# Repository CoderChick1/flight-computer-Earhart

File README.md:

# flight-computer-Earhart
Flight computer capable of dual deploy of pyrotechnics, gps tracking, and data-logging. Live telemetry can be implemented with an external board, meant for use with an Adafruit LoRa 433MHz module.

This is my first ever attempt at a pcb- had a lot of problems

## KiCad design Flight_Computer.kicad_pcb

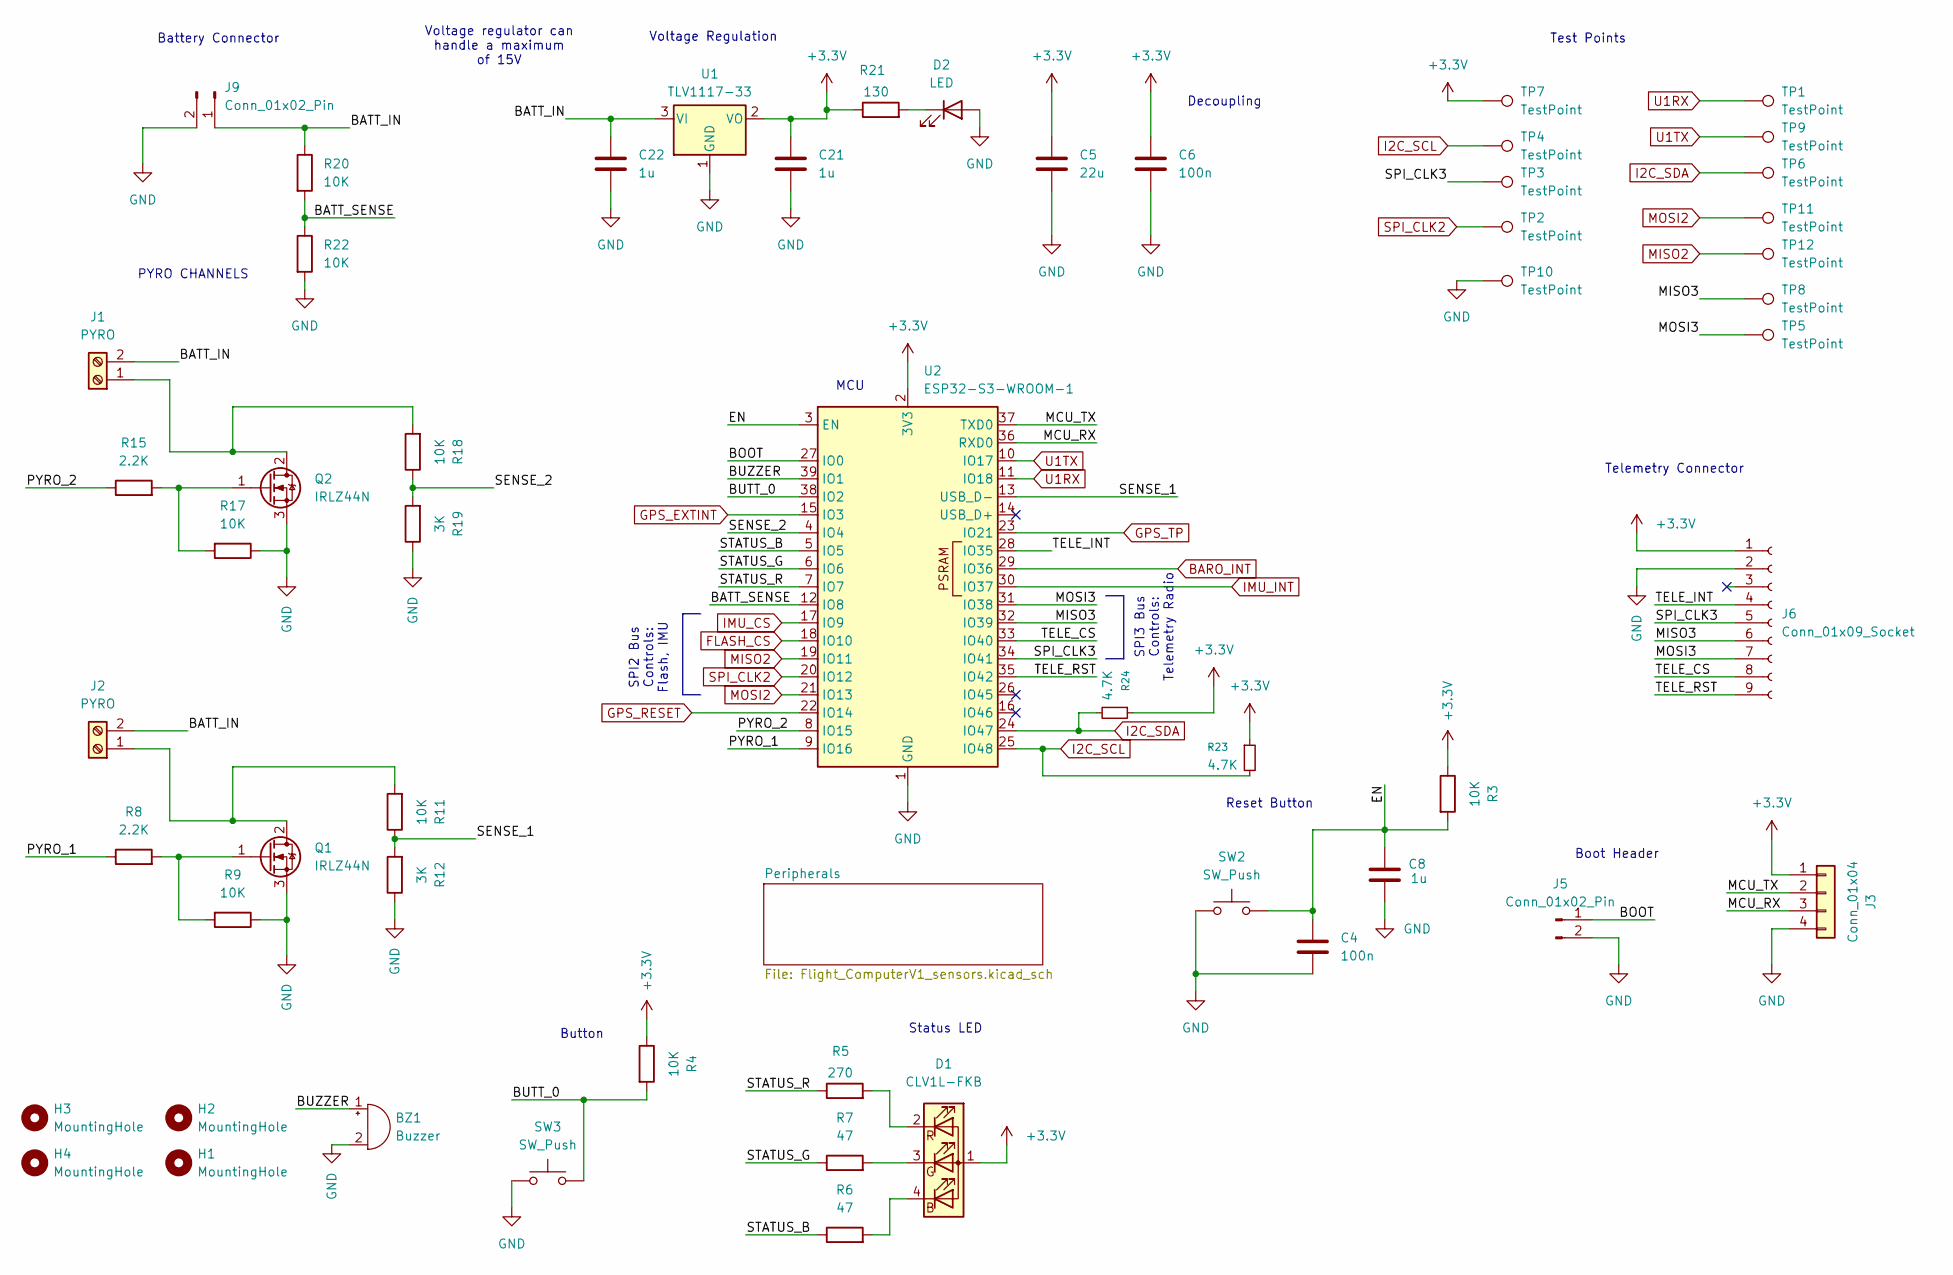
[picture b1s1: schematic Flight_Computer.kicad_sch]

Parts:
BZ1: Buzzer; Buzzer_12x9.5RM7.6
C4, C6: 100n; C_0805_2012Metric
C5: 22u; C_0805_2012Metric
C8, C21, C22: 1u; C_0805_2012Metric
D1: CLV1L-FKB; LED_Cree-PLCC4_3.2x2.8mm_CCW
D2: LED; LED_0603_1608Metric
H1, H2, H3, H4: MountingHole; MountingHole_3mm
J1, J2: PYRO; 282837-2_TYC
J3: Conn_01x04; PinHeader_1x04_P2.54mm_Vertical
J5: Conn_01x02_Pin; PinHeader_1x02_P2.54mm_Vertical
J6: Conn_01x09_Socket; PinSocket_1x09_P2.54mm_Vertical
J9: Conn_01x02_Pin; JST_PH_B2B-PH-K_1x02_P2.00mm_Vertical
Q1, Q2: IRLZ44N; TO-220-3_Vertical
R3, R4, R9, R11, R17, R18, R20, R22: 10K; R_0805_2012Metric
R5: 270; R_0805_2012Metric
R6, R7: 47; R_0805_2012Metric
R8, R15: 2.2K; R_0805_2012Metric
R12, R19: 3K; R_0805_2012Metric
R21: 130; R_0805_2012Metric
R23, R24: 4.7K; R_0805_2012Metric
SW2, SW3: SW_Push; SW_SPST_PTS810
TP1, TP2, TP3, TP4, TP5, TP6, TP7, TP8, TP9, TP10, TP11, TP12: TestPoint; TestPoint_Pad_D2.0mm
U1: TLV1117-33; SOT-223-3_TabPin2
U2: ESP32-S3-WROOM-1

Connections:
+3.3V: C5.1, C6.1, C21.1, D1.1 (A), J3.1, J6.1, R3.1, R4.1, R21.1, R23.1, R24.1, TP7.1, U1.2 (VO), U2.2 (3V3); also elsewhere on the board
/BATT_IN: C22.1, J1.2, J2.2, J9.1, R20.1, U1.3 (VI)
/BATT_SENSE: R20.2, R22.1, U2.12 (IO8)
/BOOT: J5.1, U2.27 (IO0)
/BUTT_0: R4.2, SW3.2, U2.38 (IO2)
/BUZZER: BZ1.1 (+), U2.39 (IO1)
/EN: C4.1, C8.2, R3.2, SW2.2, U2.3 (EN)
/MCU_RX: J3.3, U2.36 (RXD0)
/MCU_TX: J3.2, U2.37 (TXD0)
/MISO3: J6.6, TP8.1, U2.32 (IO39)
/MOSI3: J6.7, TP5.1, U2.31 (IO38)
/PYRO_1: R8.1, U2.9 (IO16)
/PYRO_2: R15.1, U2.8 (IO15)
/SENSE_1: R11.1, R12.2, U2.13 (USB_D-)
/SENSE_2: R18.1, R19.2, U2.4 (IO4)
/SPI_CLK3: J6.5, TP3.1, U2.34 (IO41)
/STATUS_B: R6.1, U2.5 (IO5)
/STATUS_G: R7.1, U2.6 (IO6)
/STATUS_R: R5.1, U2.7 (IO7)
/TELE_CS: J6.8, U2.33 (IO40)
/TELE_INT: J6.4, U2.28 (IO35)
/TELE_RST: J6.9, U2.35 (IO42)
BARO_INT: U2.29 (IO36); also elsewhere on the board
FLASH_CS: U2.18 (IO10); also elsewhere on the board
GND: BZ1.2 (-), C4.2, C5.2, C6.2, C8.1, C21.2, C22.2, D2.2 (A), J3.4, J5.2, J6.2, J9.2, Q1.3 (S), Q2.3 (S), R9.1, R12.1, R17.1, R19.1, R22.2, SW2.1, SW3.1, TP10.1, U1.1 (GND), U2.1 (GND), U2.40 (GND), U2.41 (GND); also elsewhere on the board
GPS_EXTINT: U2.15 (IO3); also elsewhere on the board
GPS_RESET: U2.22 (IO14); also elsewhere on the board
GPS_TP: U2.23 (IO21); also elsewhere on the board
I2C_SCL: R23.2, TP4.1, U2.25 (IO48); also elsewhere on the board
I2C_SDA: R24.2, TP6.1, U2.24 (IO47); also elsewhere on the board
IMU_CS: U2.17 (IO9); also elsewhere on the board
IMU_INT: U2.30 (IO37); also elsewhere on the board
MISO2: TP12.1, U2.19 (IO11); also elsewhere on the board
MOSI2: TP11.1, U2.21 (IO13); also elsewhere on the board
unnamed: D1.4 (BK), R6.2
unnamed: D1.3 (GK), R7.2
unnamed: D1.2 (RK), R5.2
unnamed: D2.1 (K), R21.2
unnamed: J1.1, Q2.2 (D), R18.2
unnamed: J2.1, Q1.2 (D), R11.2
unnamed: Q1.1 (G), R8.2, R9.2
unnamed: Q2.1 (G), R15.2, R17.2
SPI_CLK2: TP2.1, U2.20 (IO12); also elsewhere on the board
U1RX: TP1.1, U2.11 (IO18); also elsewhere on the board
U1TX: TP9.1, U2.10 (IO17); also elsewhere on the board

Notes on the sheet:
Status LED
Reset Button
Boot Header
Voltage regulator can handle a maximum of 15V
Battery Connector
Button
PYRO CHANNELS
Decoupling
SPI2 Bus Controls: Flash, IMU
Telemetry Connector
Test Points
Voltage Regulation
MCU
SPI3 Bus Controls: Telemetry Radio

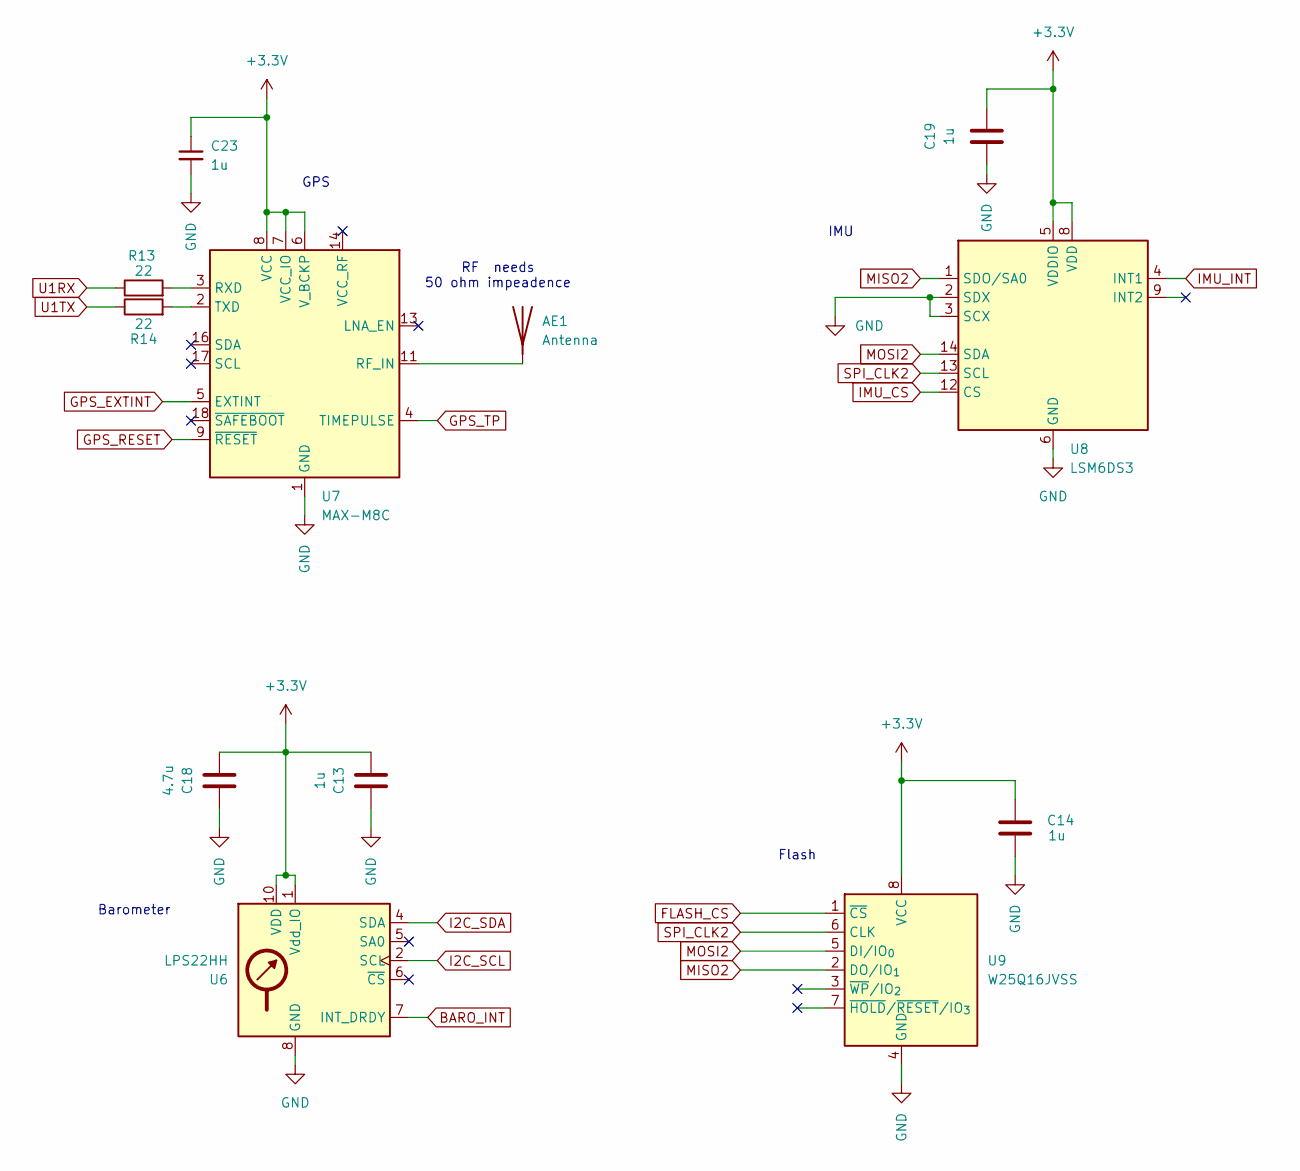
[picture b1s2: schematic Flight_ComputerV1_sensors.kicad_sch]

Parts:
AE1: Antenna; Untitled
C13, C14, C19, C23: 1u; C_0805_2012Metric
C18: 4.7u; C_0805_2012Metric
R13, R14: 22; R_0805_2012Metric
U6: LPS22HH; ST_HLGA-10_2x2mm_P0.5mm_LayoutBorder3x2y
U7: MAX-M8C; ublox_MAX
U8: LSM6DS3; LGA-14_3x2.5mm_P0.5mm_LayoutBorder3x4y
U9: W25Q16JVSS; SOIC-8_5.3x5.3mm_P1.27mm

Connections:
+3.3V: C13.1, C14.2, C18.1, C19.2, C23.1, U6.1 (Vdd_IO), U6.10 (VDD), U7.6 (V_BCKP), U7.7 (VCC_IO), U7.8 (VCC), U8.5 (VDDIO), U8.8 (VDD), U9.8 (VCC); also elsewhere on the board
BARO_INT: U6.7 (INT_DRDY); also elsewhere on the board
FLASH_CS: U9.1 (~CS); also elsewhere on the board
GND: C13.2, C14.1, C18.2, C19.1, C23.2, U6.3 (GND), U6.8 (GND), U6.9 (GND), U7.1 (GND), U7.10 (GND), U7.12 (GND), U8.2 (SDX), U8.3 (SCX), U8.6 (GND), U8.7 (GND), U9.4 (GND); also elsewhere on the board
GPS_EXTINT: U7.5 (EXTINT); also elsewhere on the board
GPS_RESET: U7.9 (~RESET); also elsewhere on the board
GPS_TP: U7.4 (TIMEPULSE); also elsewhere on the board
I2C_SCL: U6.2 (SCL); also elsewhere on the board
I2C_SDA: U6.4 (SDA); also elsewhere on the board
IMU_CS: U8.12 (CS); also elsewhere on the board
IMU_INT: U8.4 (INT1); also elsewhere on the board
MISO2: U8.1 (SDO/SA0), U9.2 (DO/IO_{1}); also elsewhere on the board
MOSI2: U8.14 (SDA), U9.5 (DI/IO_{0}); also elsewhere on the board
unnamed: AE1.1 (A), U7.11 (RF_IN)
unnamed: R13.2, U7.3 (RXD)
unnamed: R14.2, U7.2 (TXD)
SPI_CLK2: U8.13 (SCL), U9.6 (CLK); also elsewhere on the board
U1RX: R13.1; also elsewhere on the board
U1TX: R14.1; also elsewhere on the board

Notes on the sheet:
GPS
IMU
RF needs 50 ohm impeadence
Flash
Barometer

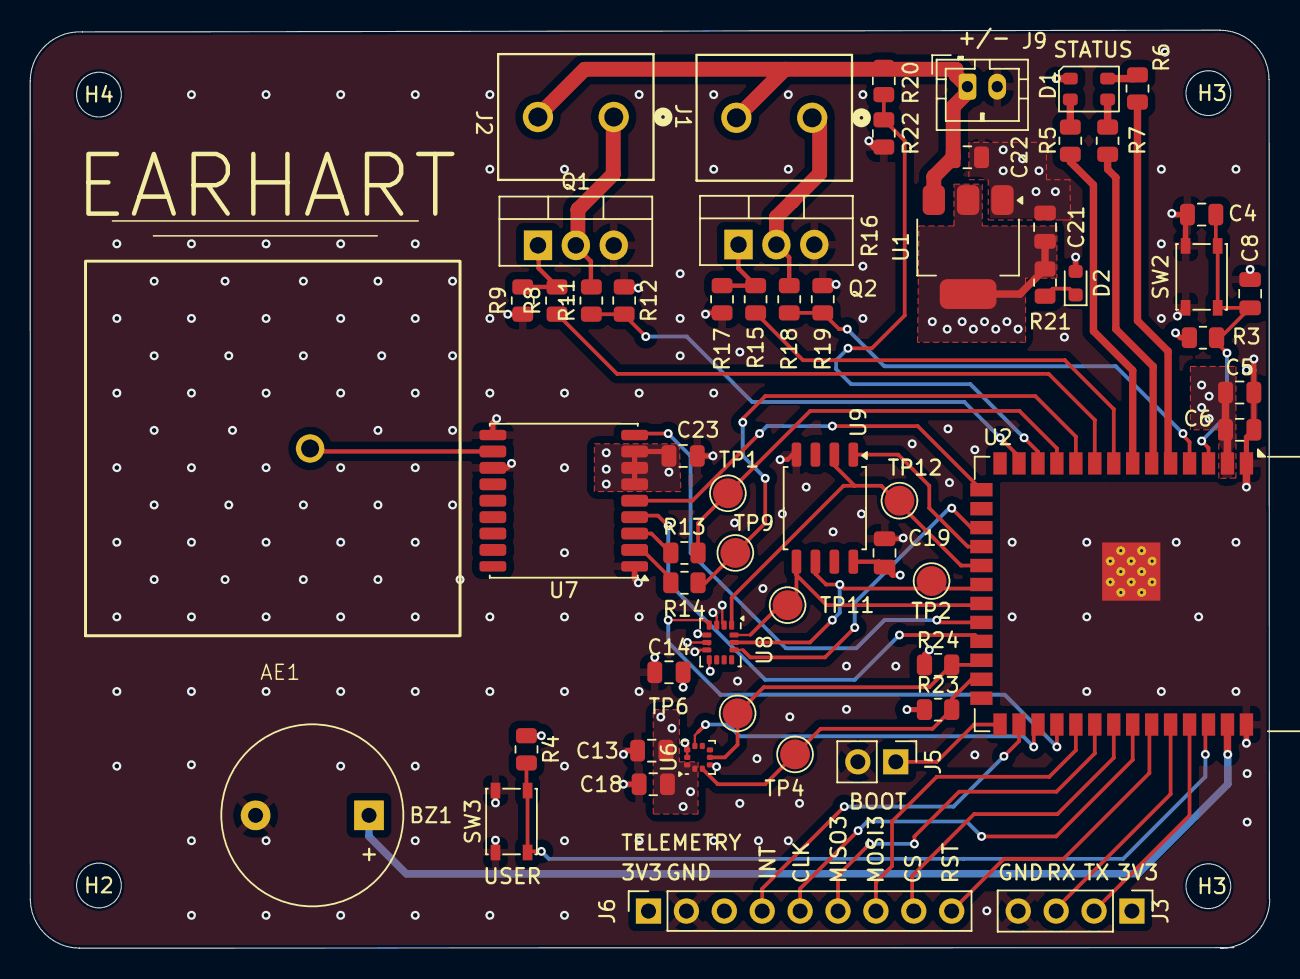
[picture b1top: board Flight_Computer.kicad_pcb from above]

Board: 4 copper layers, 83.1 x 61.5 mm, 62 parts (0 on the bottom side), 48 nets.

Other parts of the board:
H3#2: MountingHole; MountingHole_3mm

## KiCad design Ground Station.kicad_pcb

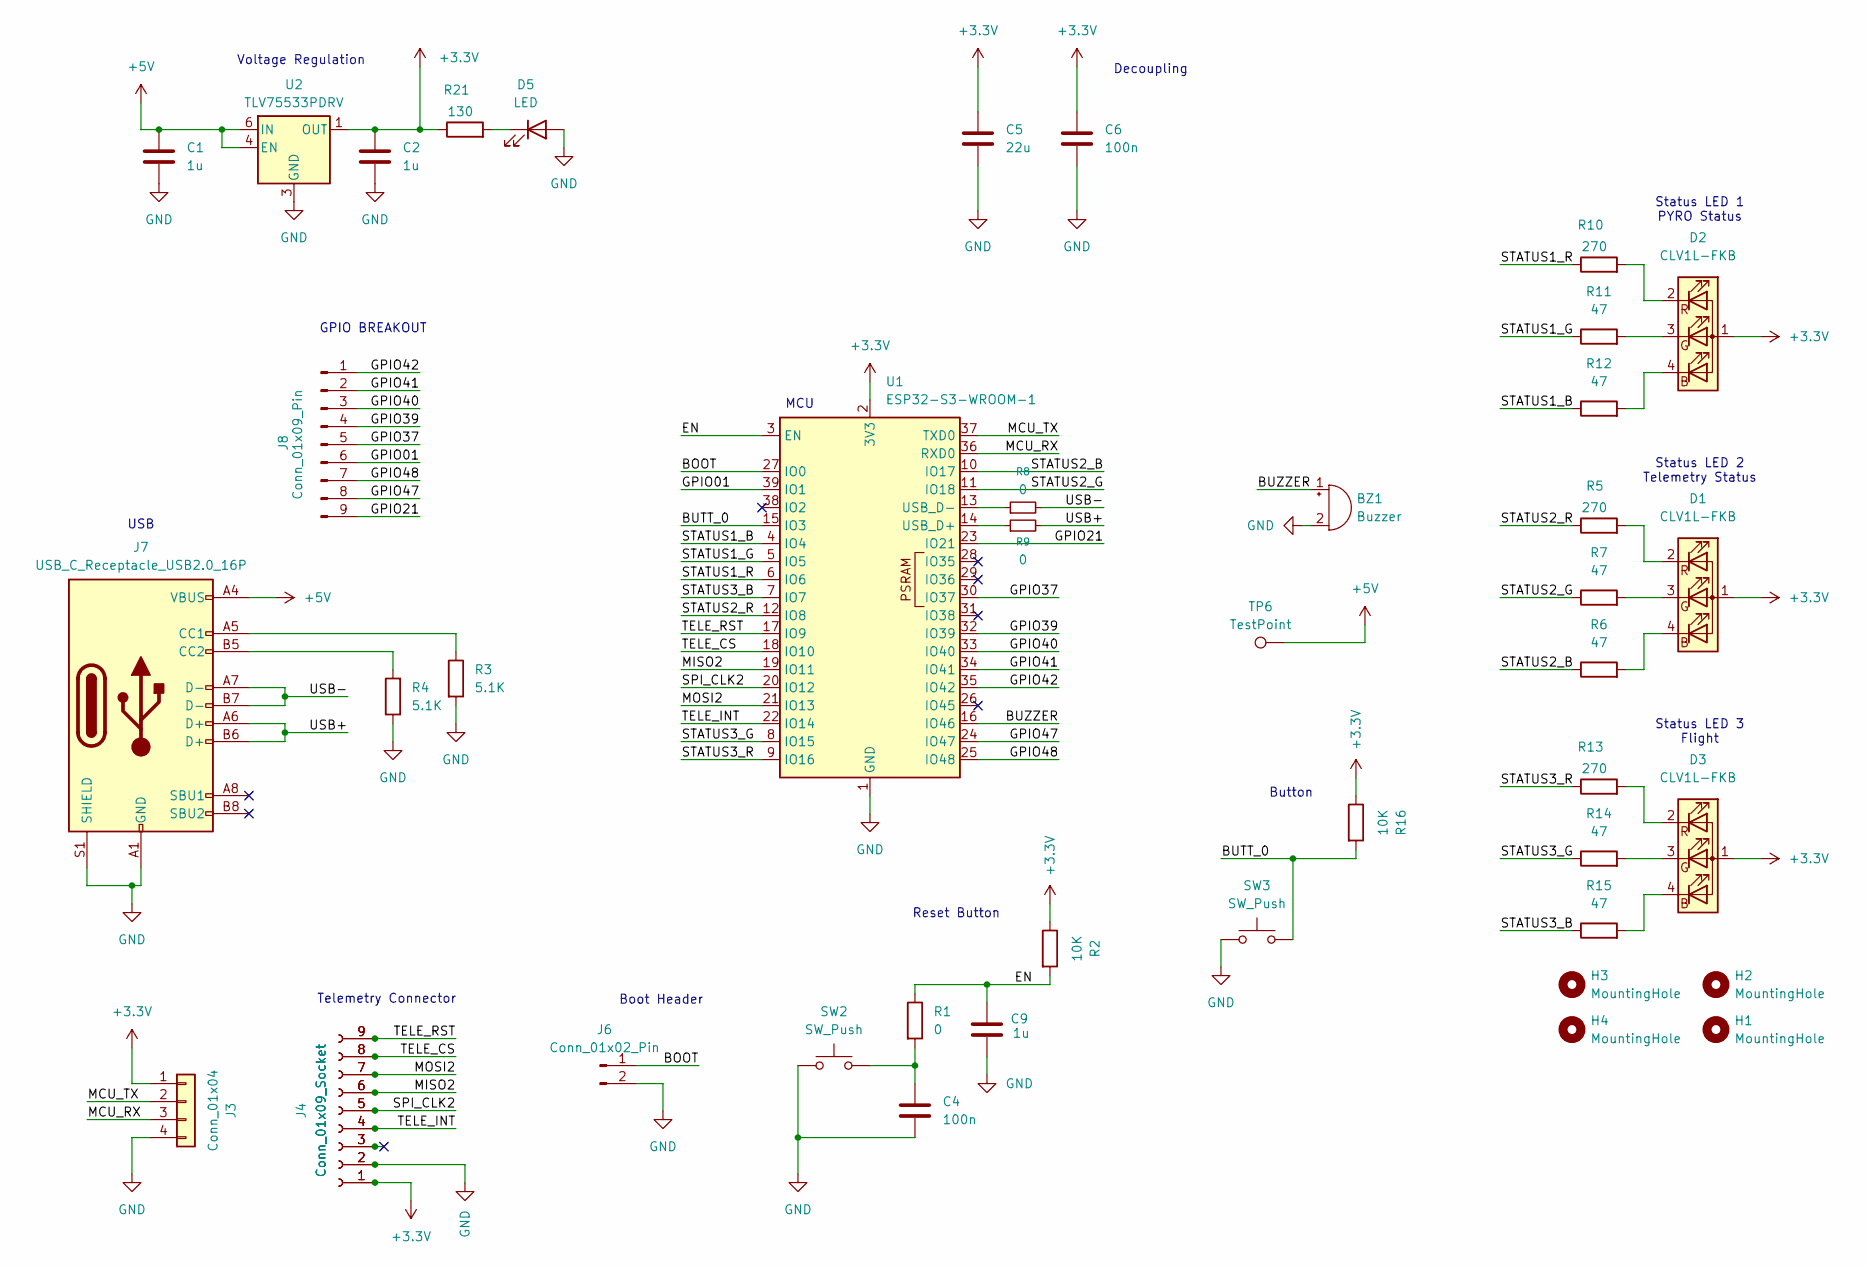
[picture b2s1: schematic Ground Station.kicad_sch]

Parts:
BZ1: Buzzer; Buzzer_12x9.5RM7.6
C1, C2, C9: 1u; C_0805_2012Metric
C4, C6: 100n; C_0805_2012Metric
C5: 22u; C_0805_2012Metric
D1, D2, D3: CLV1L-FKB; LED_Cree-PLCC4_3.2x2.8mm_CCW
D5: LED; LED_0603_1608Metric
H1, H2, H3, H4: MountingHole; MountingHole_3mm
J3: Conn_01x04; PinHeader_1x04_P2.54mm_Vertical
J4, J5: Conn_01x09_Socket; PinSocket_1x09_P2.54mm_Vertical
J6: Conn_01x02_Pin; PinHeader_1x02_P2.54mm_Vertical
J7: USB_C_Receptacle_USB2.0_16P; USB_C_Receptacle_GCT_USB4105-xx-A_16P_TopMnt_Horizontal
J8: Conn_01x09_Pin; PinHeader_1x09_P2.54mm_Vertical
R1, R8, R9: 0; R_0805_2012Metric
R2, R16: 10K; R_0805_2012Metric
R3, R4: 5.1K; R_0805_2012Metric
R5, R10, R13: 270; R_0805_2012Metric
R6, R7, R11, R12, R14, R15: 47; R_0805_2012Metric
R21: 130; R_0805_2012Metric
SW2, SW3: SW_Push; SW_SPST_PTS810
TP6: TestPoint; TestPoint_Pad_D2.0mm
U1: ESP32-S3-WROOM-1
U2: TLV75533PDRV; SOT-223

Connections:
+3.3V: C2.1, C5.1, C6.1, D1.1 (A), D2.1 (A), D3.1 (A), J3.1, J4.1, J5.1, R2.1, R16.1, R21.1, U1.2 (3V3), U2.1 (OUT)
+5V: C1.1, J7.A4 (VBUS), J7.A9 (VBUS), J7.B4 (VBUS), J7.B9 (VBUS), TP6.1, U2.4 (EN), U2.6 (IN)
/BOOT: J6.1, U1.27 (IO0)
/BUTT_0: R16.2, SW3.2, U1.15 (IO3)
/BUZZER: BZ1.1 (+), U1.16 (IO46)
/EN: C9.2, R1.1, R2.2, U1.3 (EN)
/GPIO01: J8.6, U1.39 (IO1)
/GPIO21: J8.9, U1.23 (IO21)
/GPIO37: J8.5, U1.30 (IO37)
/GPIO39: J8.4, U1.32 (IO39)
/GPIO40: J8.3, U1.33 (IO40)
/GPIO41: J8.2, U1.34 (IO41)
/GPIO42: J8.1, U1.35 (IO42)
/GPIO47: J8.8, U1.24 (IO47)
/GPIO48: J8.7, U1.25 (IO48)
/MCU_RX: J3.3, U1.36 (RXD0)
/MCU_TX: J3.2, U1.37 (TXD0)
/MISO2: J4.6, J5.6, U1.19 (IO11)
/MOSI2: J4.7, J5.7, U1.21 (IO13)
/SPI_CLK2: J4.5, J5.5, U1.20 (IO12)
/STATUS1_B: R12.1, U1.4 (IO4)
/STATUS1_G: R11.1, U1.5 (IO5)
/STATUS1_R: R10.1, U1.6 (IO6)
/STATUS2_B: R6.1, U1.10 (IO17)
/STATUS2_G: R7.1, U1.11 (IO18)
/STATUS2_R: R5.1, U1.12 (IO8)
/STATUS3_B: R15.1, U1.7 (IO7)
/STATUS3_G: R14.1, U1.8 (IO15)
/STATUS3_R: R13.1, U1.9 (IO16)
/TELE_CS: J4.8, J5.8, U1.18 (IO10)
/TELE_INT: J4.4, J5.4, U1.22 (IO14)
/TELE_RST: J4.9, J5.9, U1.17 (IO9)
/USB+: J7.A6 (D+), J7.B6 (D+), R9.2
/USB-: J7.A7 (D-), J7.B7 (D-), R8.2
GND: BZ1.2 (-), C1.2, C2.2, C4.2, C5.2, C6.2, C9.1, D5.2 (A), J3.4, J4.2, J5.2, J6.2, J7.A1 (GND), J7.A12 (GND), J7.B1 (GND), J7.B12 (GND), J7.S1 (SHIELD), R3.2, R4.1, SW2.1, SW3.1, U1.1 (GND), U1.40 (GND), U1.41 (GND), U2.3 (GND), U2.7 (GND)
unnamed: C4.1, R1.2, SW2.2
unnamed: D1.4 (BK), R6.2
unnamed: D1.3 (GK), R7.2
unnamed: D1.2 (RK), R5.2
unnamed: D2.4 (BK), R12.2
unnamed: D2.3 (GK), R11.2
unnamed: D2.2 (RK), R10.2
unnamed: D3.4 (BK), R15.2
unnamed: D3.3 (GK), R14.2
unnamed: D3.2 (RK), R13.2
unnamed: D5.1 (K), R21.2
unnamed: J4.3, J5.3
unnamed: J7.A5 (CC1), R3.1
unnamed: J7.B5 (CC2), R4.2
unnamed: R9.1, U1.14 (USB_D+)
unnamed: R8.1, U1.13 (USB_D-)

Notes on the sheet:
Status LED 3 Flight
Telemetry Connector
Voltage Regulation
Status LED 2 Telemetry Status
Boot Header
Status LED 1 PYRO Status
MCU
Decoupling
USB
Reset Button
GPIO BREAKOUT
Button

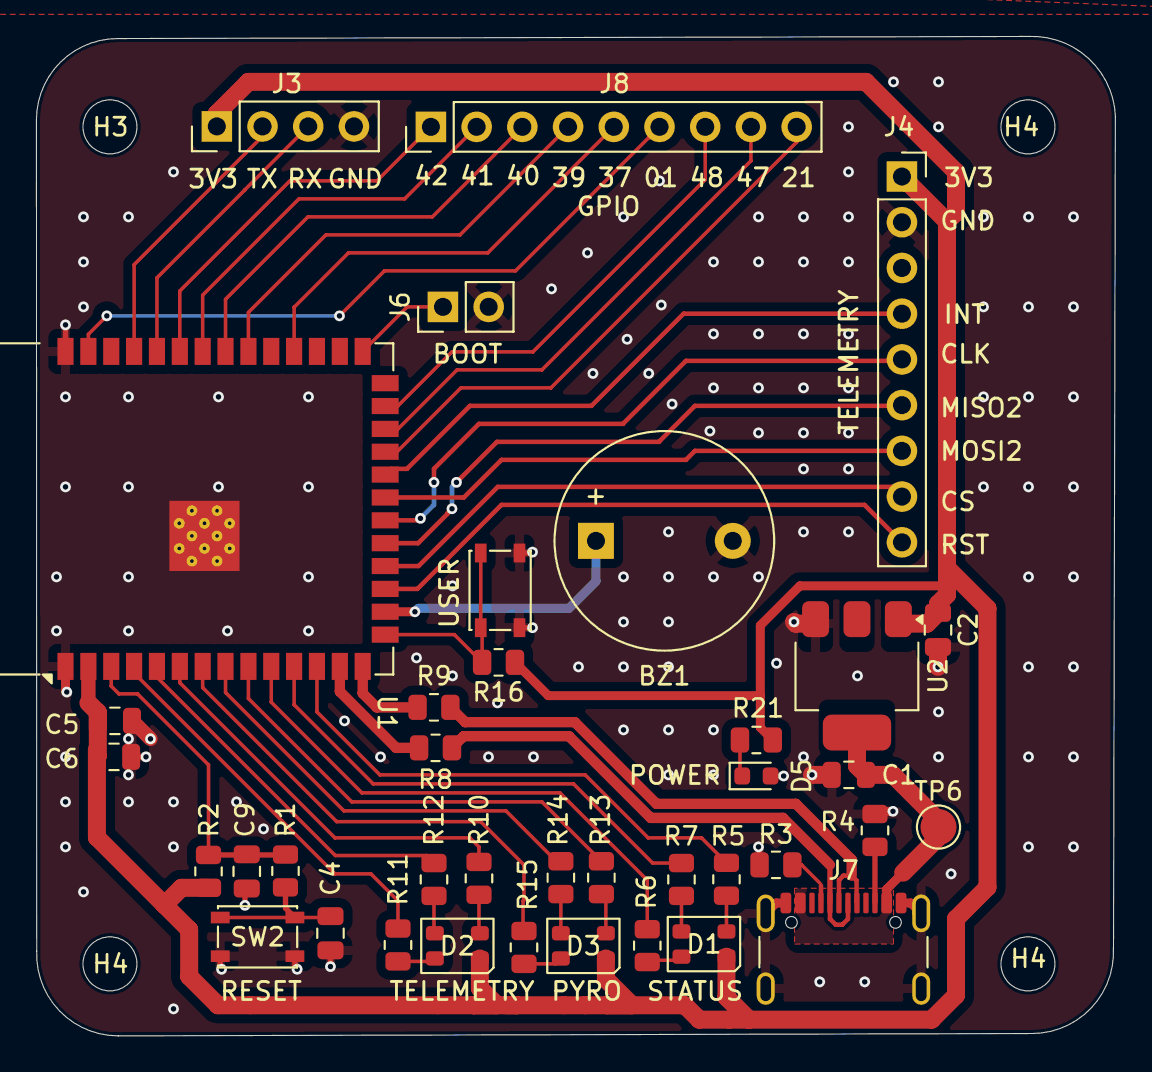
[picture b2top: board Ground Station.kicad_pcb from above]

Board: 2 copper layers, 59.9 x 55.5 mm, 42 parts (0 on the bottom side), 50 nets.

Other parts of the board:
H4#2, H4#3: MountingHole; MountingHole_3mm

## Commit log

2025-06-28 Add files via upload
    Version 1 Pcb
2025-07-01 Version 2 PCB
    Updated layout, routing
2025-07-10 Upload final pcb and schematic version
2025-07-11 Images of final pcb and schmatics
